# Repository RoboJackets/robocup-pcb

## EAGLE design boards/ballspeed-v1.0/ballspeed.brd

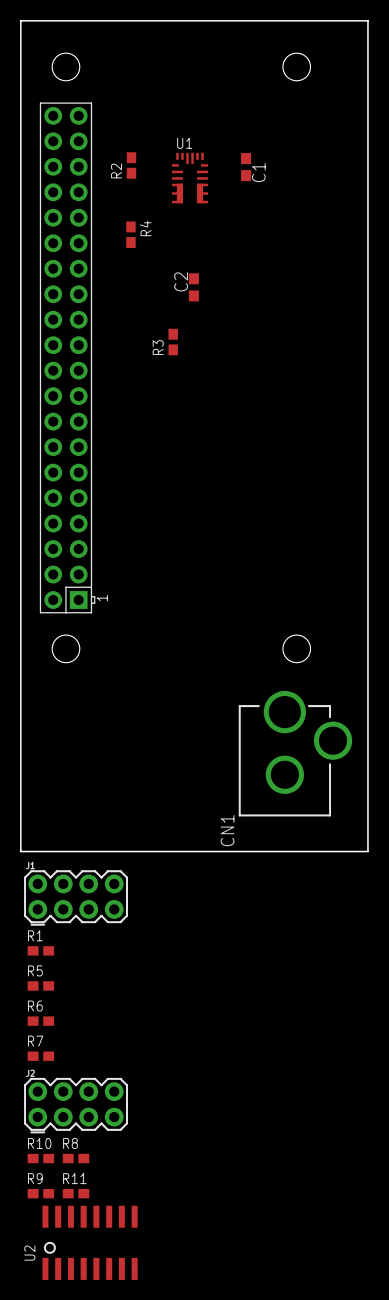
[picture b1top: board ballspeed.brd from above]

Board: 2 copper layers, 34.6 x 82.8 mm, 19 parts (0 on the bottom side), 14 nets, no tracks yet.

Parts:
C1: 10uF; C0603
C2: 22uF; C0603
CN1: DCJACK_2MM_PTH
J1, J2: 2X4
R1, R5, R6, R7: 10k; R0603W
R2: 63.4k; R0603W
R3: 160k; R0603W
R4: 30.1k; R0603W
R8, R9, R10, R11: 100; R0603W
U1: MPM3620GQV-P
U2: MCP3008SL; SOIC-16
U$2: RPI-ZERO; RASPBERRYPI_BASTELSTUBE_V13_RASPI_BOARD_B+_FULL

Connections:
+3.3V: R1.1, R5.1, R6.1, R7.1, R8.1, R9.1, R10.1, R11.1, U2.15, U2.16, U$2.1
+5V: C2.1, R3.2, U1.789, U$2.2
GND: C1.2, C2.2, CN1.GND, J1.2, J1.4, J1.6, J1.8, J2.2, J2.4, J2.6, J2.8, R2.1, R4.1, U1.3, U1.12, U1.13, U1.14, U2.9, U2.10, U2.14, U$2.9
IR1: J1.1, R1.2, U2.1, U$2.29
IR2: J1.3, R5.2, U2.2, U$2.31
IR3: J1.5, R6.2, U2.3, U$2.33
IR4: J1.7, R7.2, U2.4, U$2.35
IR6: J2.3, R9.2
unnamed: R3.1, R4.2, U1.1
unnamed: C1.1, U1.16, U1.17
unnamed: R2.2, U1.18
unnamed: J2.1, R8.2
unnamed: J2.5, R10.2
unnamed: J2.7, R11.2

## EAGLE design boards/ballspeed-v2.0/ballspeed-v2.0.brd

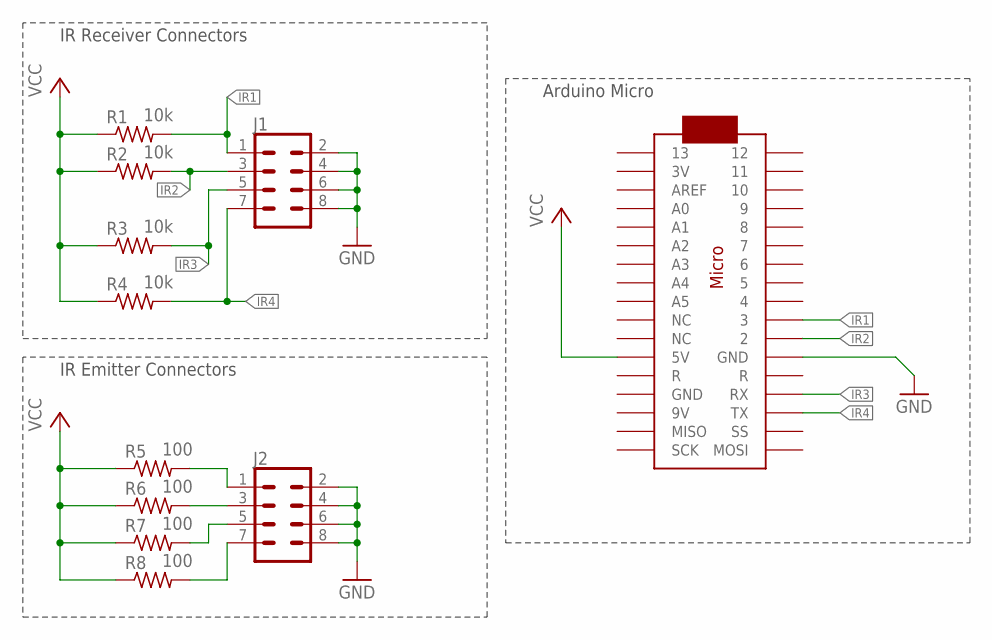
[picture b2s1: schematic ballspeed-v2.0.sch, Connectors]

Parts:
J1, J2: CONN_04X2; 2X4
R1, R2, R3, R4: 10k; R0603W
R5, R6, R7, R8: 100; R0603W
U$1: ARDUINOMICRO

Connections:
GND: J1.2, J1.4, J1.6, J1.8, J2.2, J2.4, J2.6, J2.8, U$1.P$21 (GND)
IR1: J1.1, R1.2 (PIN2), U$1.P$10 (3)
IR1-3.3V: J2.1, R5.2 (PIN2)
IR2: J1.3, R2.2 (PIN2), U$1.P$11 (2)
IR2-3.3V: J2.3, R6.2 (PIN2)
IR3: J1.5, R3.2 (PIN2), U$1.P$14 (RX)
IR3-3.3V: J2.5, R7.2 (PIN2)
IR4: J1.7, R4.2 (PIN2), U$1.P$15 (TX)
IR4-3.3V: J2.7, R8.2 (PIN2)
VCC: R1.1 (PIN1), R2.1 (PIN1), R3.1 (PIN1), R4.1 (PIN1), R5.1 (PIN1), R6.1 (PIN1), R7.1 (PIN1), R8.1 (PIN1), U$1.P$23 (5V)

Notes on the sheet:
IR Emitter Connectors
IR Receiver Connectors
Arduino Micro

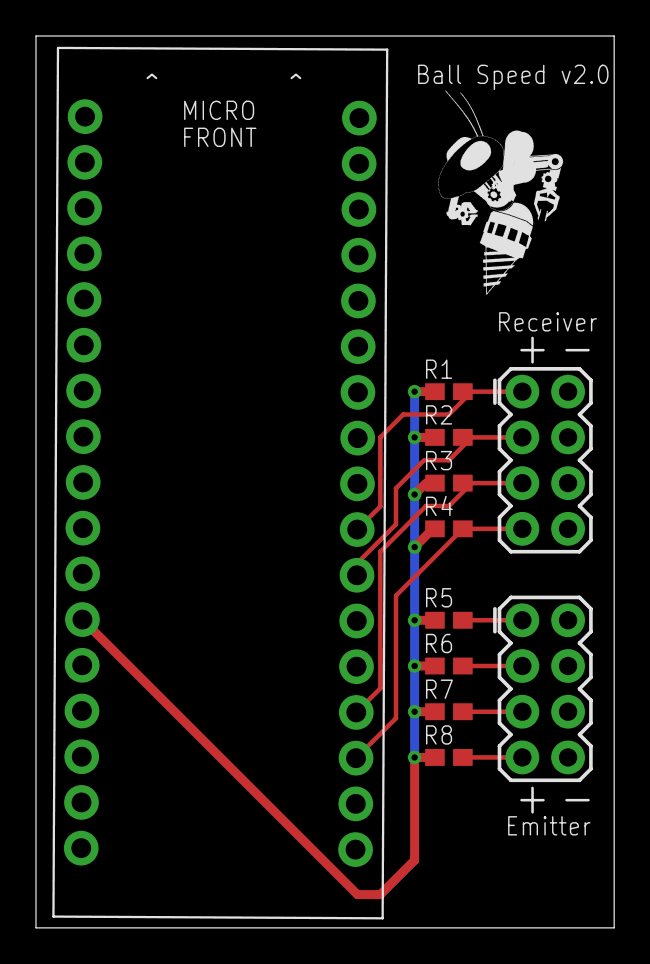
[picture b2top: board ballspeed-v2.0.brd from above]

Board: 2 copper layers, 32.1 x 49.6 mm, 12 parts (0 on the bottom side), 10 nets.

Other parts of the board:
U$3: ROBOBUZZ_0.6X

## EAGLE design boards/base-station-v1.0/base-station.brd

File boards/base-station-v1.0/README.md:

# Radio Board 2015

The 2015 radio has an mbed as the main processor and two radio boards.  We currently only use one of them, but in the future we'd like to support more than six robots at a time.  Two radio boards should give us capacity to communicate with 12 if we implement it in software.

The board also has a mini usb connector, which is used in normal operation.  The mbed's usb port is only needed for flashing new firmware or debugging.  You can use the two usb ports simultaneously.

## PCB

* Radio board connector: [87409-105LF](https://octopart.com/search?q=87409-105LF)

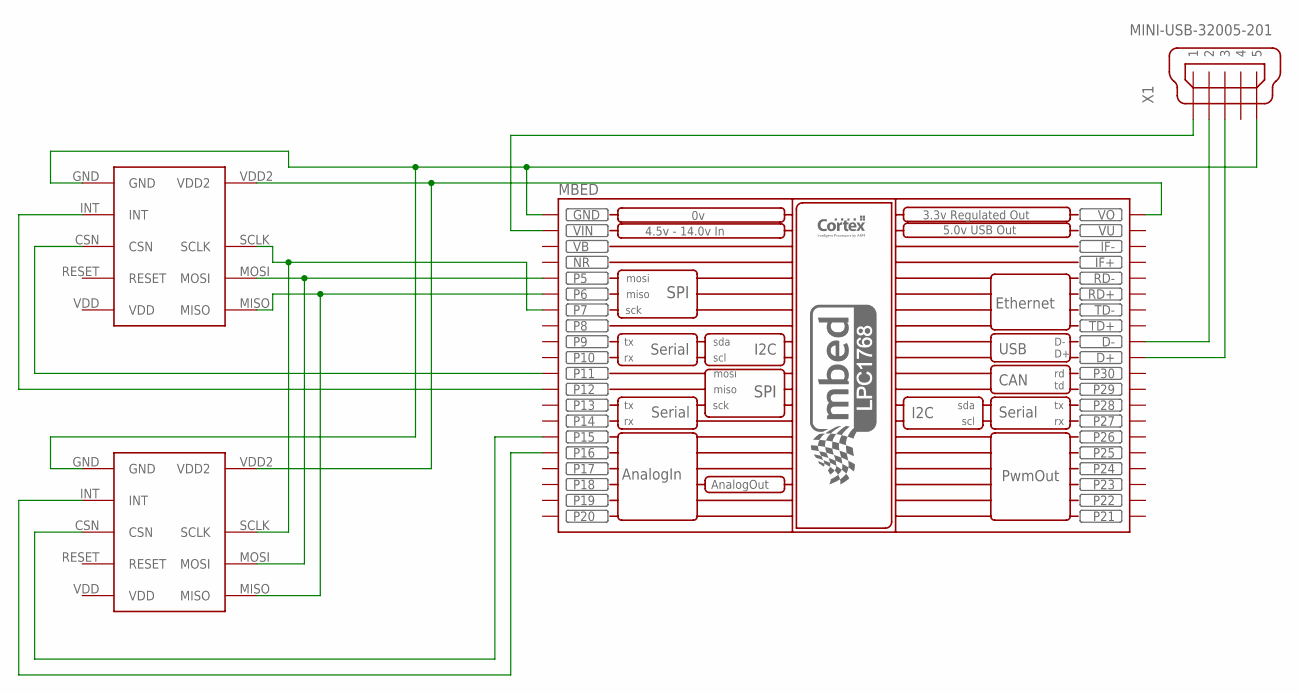
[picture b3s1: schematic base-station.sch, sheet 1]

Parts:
MBED: MBED_NXP_LPC1768; MBED-KIT
U$1, U$2: RADIOBOARD2015CONNECTOR
X1: MINI-USB-32005-201; 32005-201

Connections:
unnamed: MBED.P$5 (P5), U$1.MOSI, U$2.MOSI
unnamed: MBED.P$6 (P6), U$1.MISO, U$2.MISO
unnamed: MBED.P$15 (P15), U$2.CSN
unnamed: MBED.VIN, X1.1
unnamed: MBED.D-, X1.2
unnamed: MBED.D+, X1.3
unnamed: MBED.VOUT (VO), U$1.VDD2, U$2.VDD2
unnamed: MBED.P$12 (P12), U$1.INT
unnamed: MBED.P$11 (P11), U$1.CSN
unnamed: MBED.P$16 (P16), U$2.INT
unnamed: MBED.GND, U$1.GND, U$2.GND, X1.5
unnamed: MBED.P$7 (P7), U$1.SCLK, U$2.SCLK
VB: MBED.VB
VU: MBED.VU

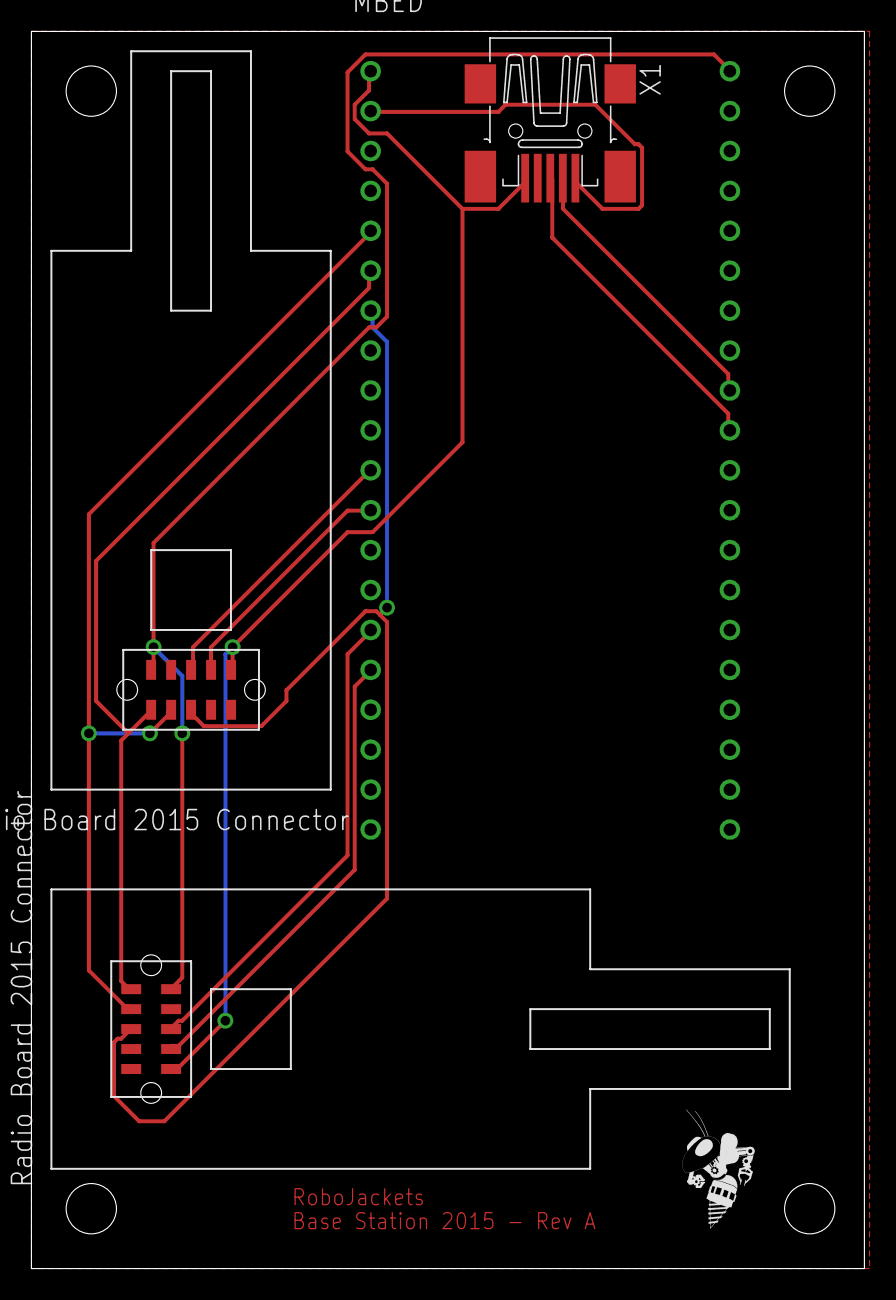
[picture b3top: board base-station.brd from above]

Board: 2 copper layers, 53.0 x 78.7 mm, 5 parts (0 on the bottom side), 12 nets.

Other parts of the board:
U$3: ROBOBUZZ0.4X; ROBOBUZZ_0.4X

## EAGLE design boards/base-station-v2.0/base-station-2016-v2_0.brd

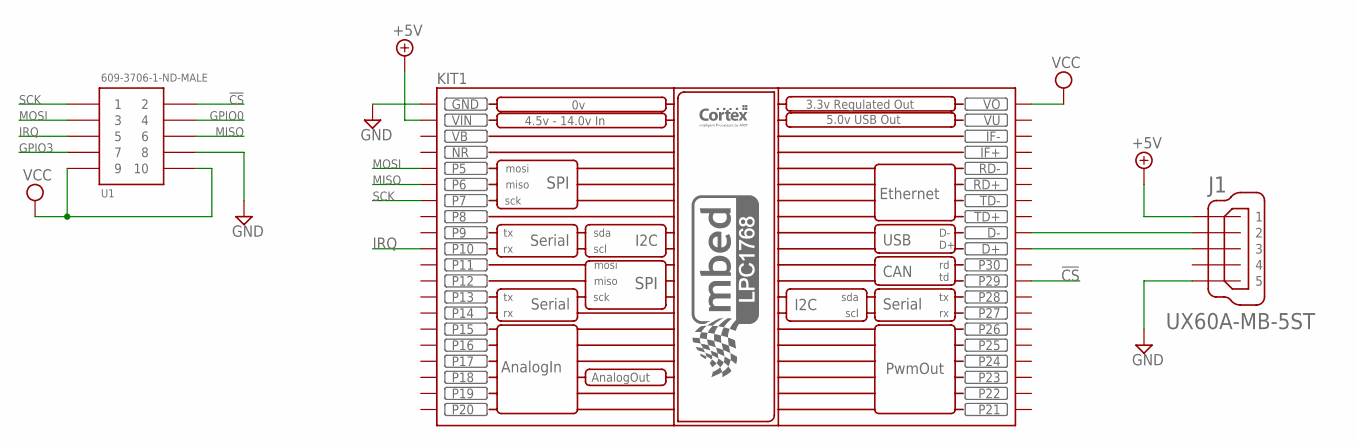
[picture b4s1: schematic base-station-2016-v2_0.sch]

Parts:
J1: UX60A-MB-5ST
KIT1: MBED_NXP_LPC1768; MBED-KIT
U1: 609-3706-1-ND-MALE; 5X2_MALE

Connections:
!CS: KIT1.P$29 (P29), U1.2
+5V: J1.1, KIT1.VIN
GND: J1.5, KIT1.GND, U1.8
GPIO0: U1.4
GPIO3: U1.7
IRQ: KIT1.P$10 (P10), U1.5
MISO: KIT1.P$6 (P6), U1.6
MOSI: KIT1.P$5 (P5), U1.3
unnamed: J1.2, KIT1.D-
unnamed: J1.3, KIT1.D+
SCK: KIT1.P$7 (P7), U1.1
VB: KIT1.VB
VCC: KIT1.VOUT (VO), U1.9, U1.10
VU: KIT1.VU

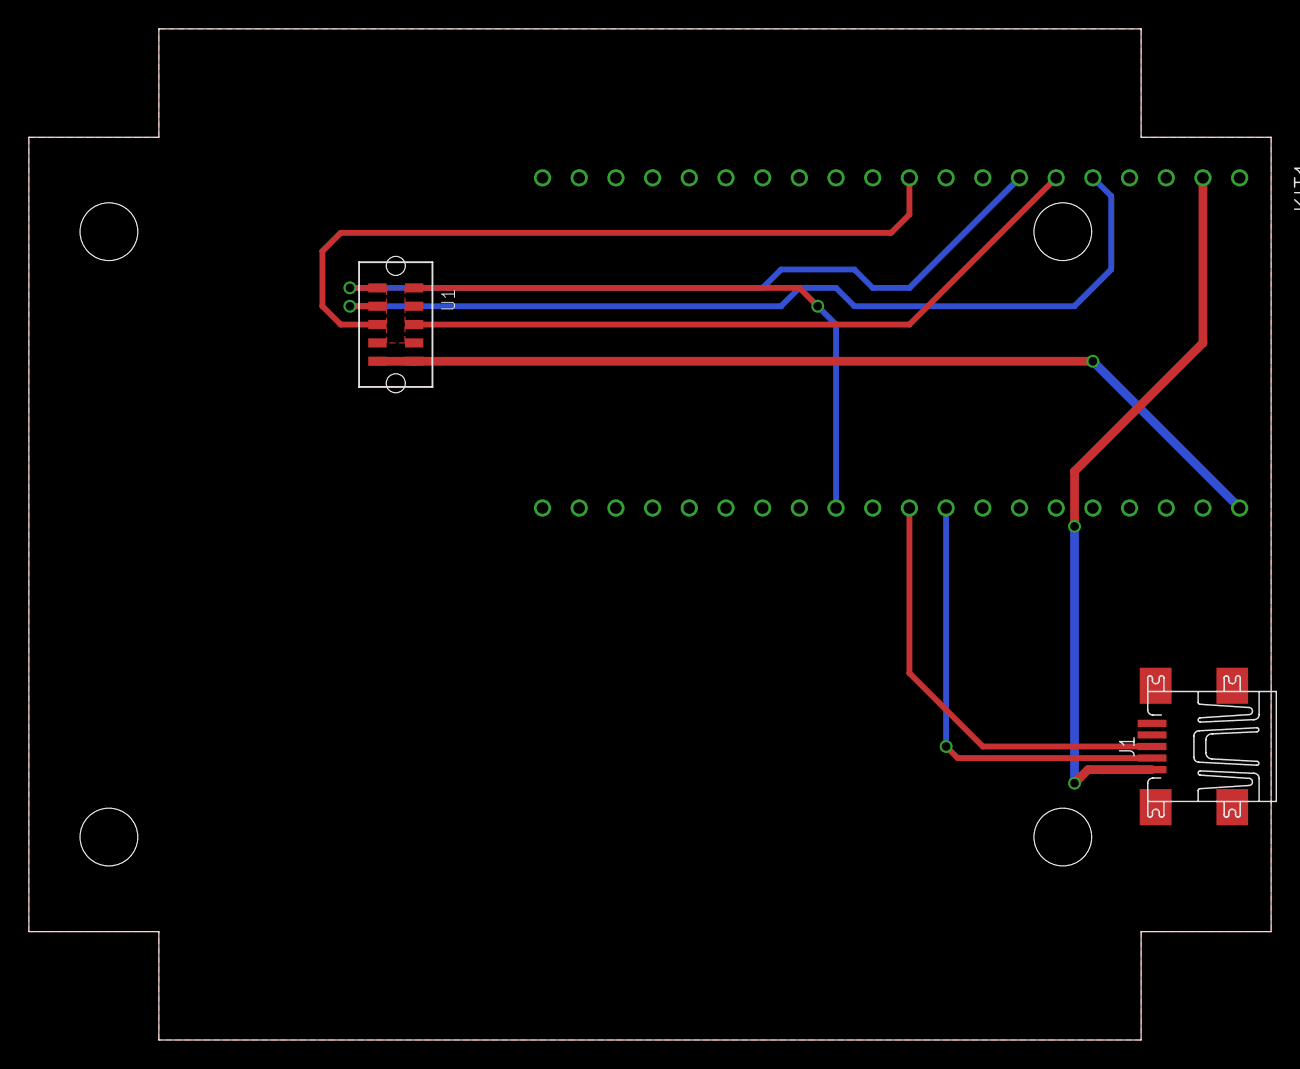
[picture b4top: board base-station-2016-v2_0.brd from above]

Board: 2 copper layers, 86.0 x 70.0 mm, 4 parts (0 on the bottom side), 10 nets.

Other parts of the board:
U$1: RADIO-2016-V1_0

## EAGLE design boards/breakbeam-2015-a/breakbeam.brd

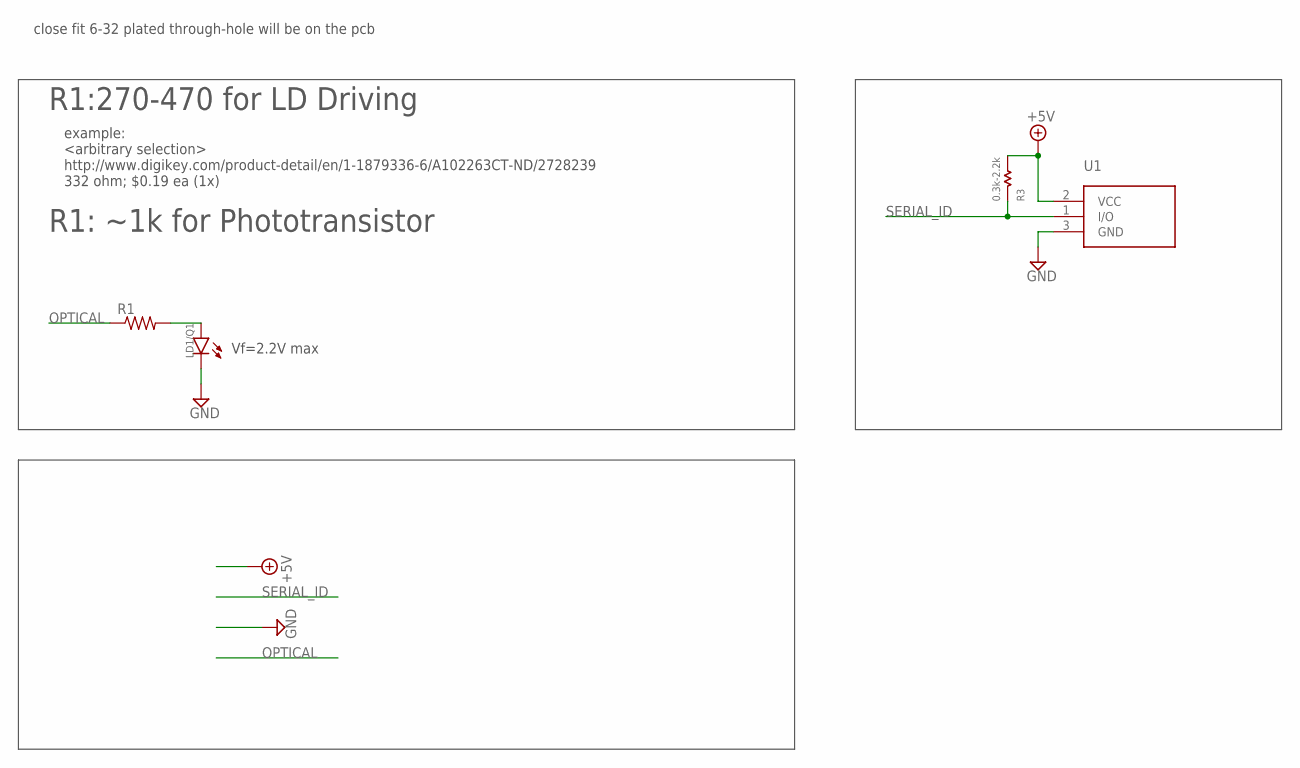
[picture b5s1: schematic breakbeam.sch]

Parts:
LD1/Q1: LD_SIDELOOK_FACEDOWNEXTRA_SHORT_LEAD_MINIMIZED; 2LEAD_H_FACEDOWN_XSHORT_MIN
R1: R-US_R0603; R0603
R3: 0.3k-2.2k; GHOST_0.075
U1: DS2411; SOT-23-3

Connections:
+5V: R3.P$2 (PIN2), U1.2 (VCC)
GND: LD1/Q1.1 (C), U1.3 (GND)
unnamed: LD1/Q1.2 (A), R1.2
OPTICAL: R1.1
SERIAL_ID: R3.P$1 (PIN1), U1.1 (I/O)

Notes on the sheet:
Vf=2.2V max
example: <arbitrary selection> http://www.digikey.com/product-detail/en/1-1879336-6/A102263CT-ND/2728239 332 ohm; $0.19 ea (1x)
close fit 6-32 plated through-hole will be on the pcb
R1:270-470 for LD Driving
R1: ~1k for Phototransistor

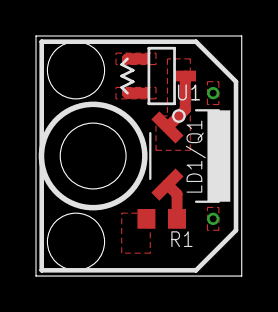
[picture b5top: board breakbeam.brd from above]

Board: 2 copper layers, 11.4 x 13.3 mm, 4 parts (0 on the bottom side), 4 nets.

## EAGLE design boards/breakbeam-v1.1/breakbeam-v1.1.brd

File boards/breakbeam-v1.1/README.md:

# Breakbeam Board
On Robot Board 

## Objective 
To indicate whether ball has been successfully captured by robot 

## Approach 
Infrared beam exists across the robot's mouth. Board detects whether the beam is broken by ball passing through it. Interfaces with kicker board.

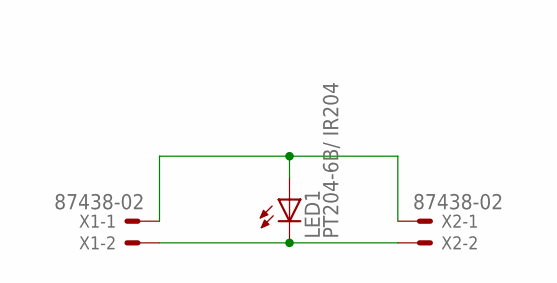
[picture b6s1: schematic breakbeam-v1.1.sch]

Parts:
LED1: PT204-6B/ IR204; LED3MM
X1, X2: 87438-02

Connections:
ANODE: LED1.A, X1.1, X2.1
CATHODE: LED1.K (C), X1.2, X2.2

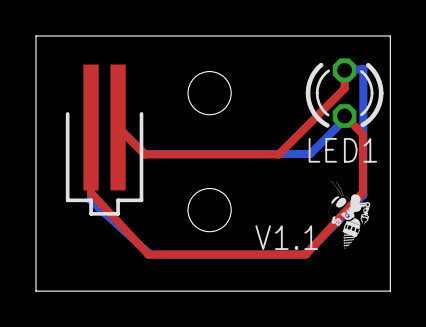
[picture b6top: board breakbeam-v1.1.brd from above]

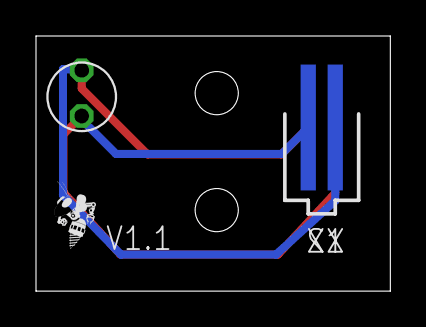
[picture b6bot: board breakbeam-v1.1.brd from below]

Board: 2 copper layers, 19.7 x 14.2 mm, 5 parts (2 on the bottom side), 2 nets.

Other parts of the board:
U$1, U$4: ROBOBUZZ_0.2X

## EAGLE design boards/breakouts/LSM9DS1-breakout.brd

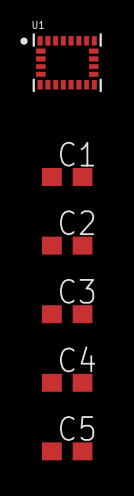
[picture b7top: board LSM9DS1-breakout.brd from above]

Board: 2 copper layers, 6 parts (0 on the bottom side), 4 nets, no tracks yet.

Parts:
C1, C4: 100nF; C0603
C2: 1uF; C0603
C3: 10uF; C0603
C5: 10nF 16V; C0603
U1: LSM9DS1; LGA-24L

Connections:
+3.3V: C1.1, C2.1, C3.1, U1.1, U1.3, U1.22, U1.23
C1: C4.1, U1.24
CAP: C5.1, U1.21
GND: C1.2, C2.2, C3.2, C4.2, C5.2, U1.14, U1.15, U1.16, U1.17, U1.18, U1.19, U1.20

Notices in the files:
parts and their libraries:
SparkFun-Connectors: Licensing: Creative Commons ShareAlike 4.0 International - https://creativecommons.org/licenses/by-sa/4.0
